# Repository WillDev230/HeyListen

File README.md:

<div align="center">

</div>
<h1></h1>
<div align="center">
HeyListen es un proyecto el cual busca disminuir la brecha de desigualdad, especificamente en el sector de las personas con nula o baja visibilidad en un contexto laboral, para brindarles la misma capacidad de ser eficientes que tienen las demas personas.
Lo lograremos brindandoles comodidades para encontrar objetos o lugares  especificos en las oficinas mediante un sonido 
</div>

<h1>Integrantes</h1>

|Integrantes   | Foto           | 
|    :---:     |     :---:      |    
| <h3>WILLIAM DAVID PINZON TORRES</h3> ||
| <h3>JOSE DANIEL BERNAL MORENO</h3>     |     |
| <h3>JUAN ESTEBAN MOZO MIGUEZ</h3>    |    |

<h1>Objetivos</h1>

* Aprender, reforzar y poner en practica conocimientos propios de la electronica
* Adquirir habilidades de liderazgo y resolucion de problemas en trabajos grupales
* adquirir habilidades de comunicacion inalambrica

<h1>Avance</h1>

* ### Caja Negra
   
* ### Caja Negra Con Tecnologia
   
  <p>Para entender mejor, se puede ver los bocetos de abajo, en especial el ultimo. </p> 
* ### Bocetos

* ### Boceto conexiones 

 * ### Boceto mecanismo 

<h1>Funcionamiento</h1>
consta de una serie de pulsadores con inscripciones en braile para su identificacion, que al ser accionados emitiran una señal, que al ser captada por otro receptor emitira un sonido durante un lapso de tiempo de 6 segundos, para que el usuario pueda ubicar su el elemento desedado
  
<h1>Aplicaciones</h1>
Las aplicaciones especificas pueden ser distintas y muy variadas pero para que en verdad sea de gran utilidad se presentan tres aplicaciones. 

### 1. Lazarillo 
Ponerle un rastreador a un baston sera de gran utilidad, pues este es un objeto relevante para las personajes de baja vision, y tambien un objeto que se puede caer o perder facilmente. No obstante para esto tendriamos que hacer que el dispositivo que tiene el boton sea movil, es decir que sea comodo y que no sea tan grande lo que puede ser un reto. 

Ejemplo: 

### 2. Controle del televisor 
De la misma manera que el anterior, estos elementos son muy faciles de perder o de refundir puesto que se utilizan bastante, entonces ponerles un rastreador a estos seria de buena utlidad

### 3. Llaves
Aunque podria ser incomodo, las llaves son uno de los elementos que mas se refunden, entonces ponerle un rastreador a las llaves puede ser muy util para una persona de baja vision. Asimismo estos elementos son demasiados importantes en la vida de las personas entonces poner un rastreador seria positivo.

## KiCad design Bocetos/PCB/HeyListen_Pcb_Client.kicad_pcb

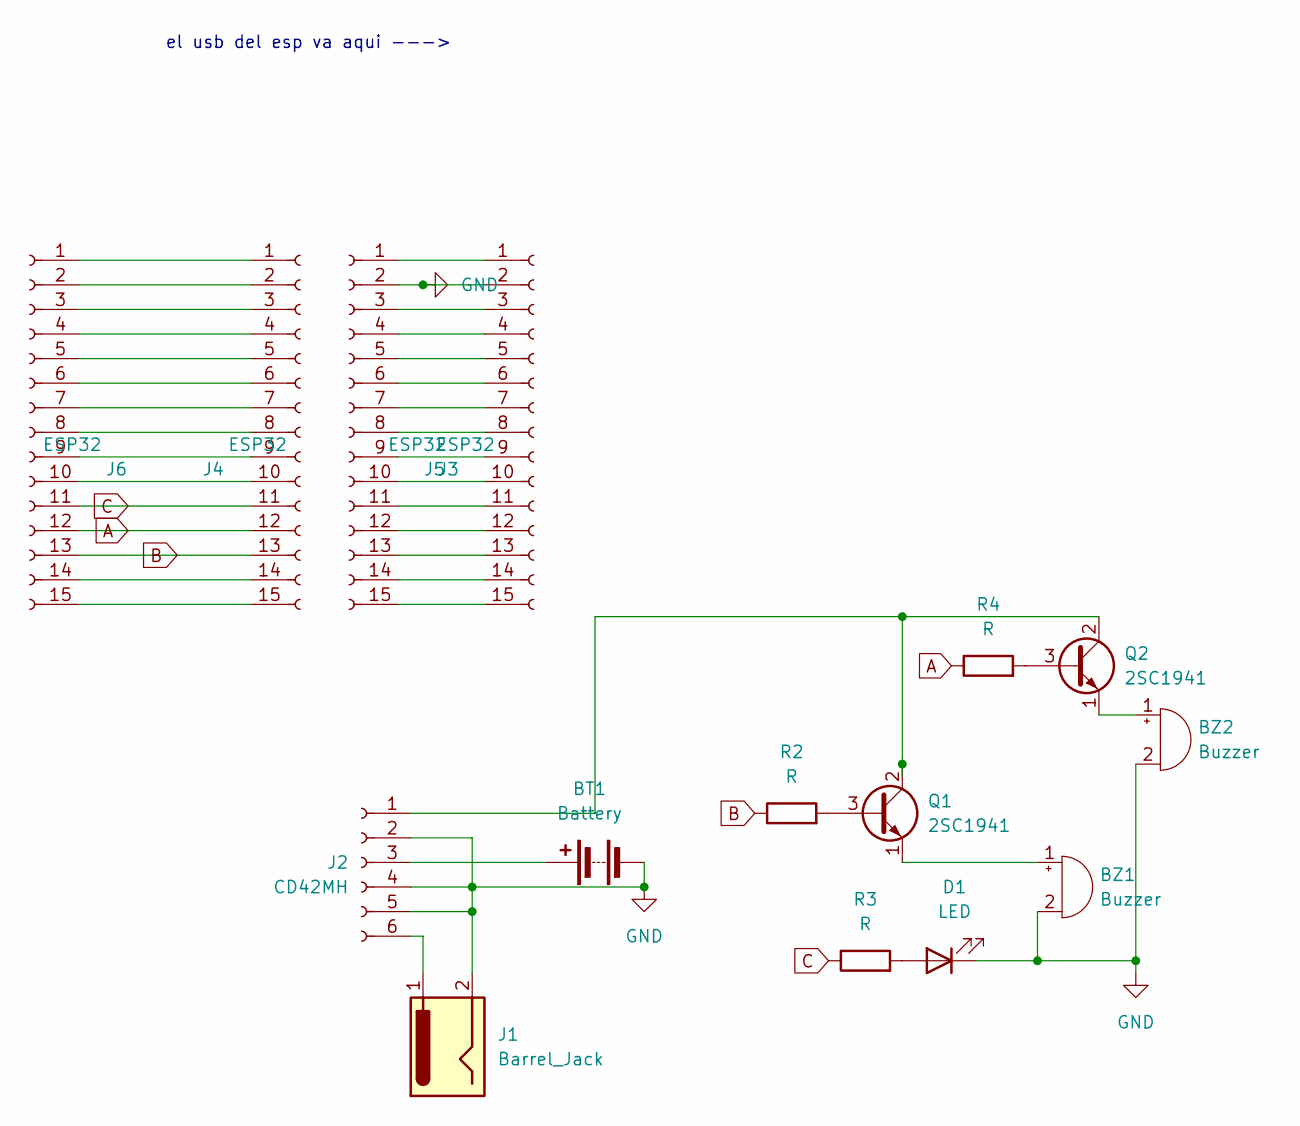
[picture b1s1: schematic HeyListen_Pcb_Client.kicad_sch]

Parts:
BT1: Battery; BatteryHolder_MPD_BH-18650-PC2
BZ1, BZ2: Buzzer; MagneticBuzzer_ProSignal_ABT-410-RC
D1: LED; LED_D3.0mm
J1: Barrel_Jack; BarrelJack_Horizontal
J2: CD42MH; PinSocket_1x06_P2.00mm_Vertical
J3, J4, J5, J6: ESP32; PinSocket_1x15_P2.00mm_Vertical
Q1, Q2: 2SC1941; TO-92_Inline
R2, R3, R4: R; R_Axial_DIN0411_L9.9mm_D3.6mm_P15.24mm_Horizontal

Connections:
A: J4.12, J6.12, R4.1
B: J4.13, J6.13, R2.1
C: J4.11, J6.11, R3.1
GND: BT1.2 (-), BZ1.2 (+), BZ2.2 (+), D1.1 (K), J1.2, J2.2, J2.4, J2.5, J3.2, J5.2
unnamed: BT1.1 (+), J2.3
unnamed: BZ1.1 (-), Q1.1 (E)
unnamed: BZ2.1 (-), Q2.1 (E)
unnamed: D1.2 (A), R3.2
unnamed: J2.1, Q1.2 (C), Q2.2 (C)
unnamed: J1.1, J2.6
unnamed: J3.1, J5.1
unnamed: J3.3, J5.3
unnamed: J3.4, J5.4
unnamed: J3.5, J5.5
unnamed: J3.6, J5.6
unnamed: J3.7, J5.7
unnamed: J3.8, J5.8
unnamed: J3.9, J5.9
unnamed: J3.10, J5.10
unnamed: J3.11, J5.11
unnamed: J3.12, J5.12
unnamed: J3.13, J5.13
unnamed: J3.14, J5.14
unnamed: J3.15, J5.15
unnamed: J4.1, J6.1
unnamed: J4.2, J6.2
unnamed: J4.3, J6.3
unnamed: J4.4, J6.4
unnamed: J4.5, J6.5
unnamed: J4.6, J6.6
unnamed: J4.7, J6.7
unnamed: J4.8, J6.8
unnamed: J4.9, J6.9
unnamed: J4.10, J6.10
unnamed: J4.14, J6.14
unnamed: J4.15, J6.15
unnamed: Q1.3 (B), R2.2
unnamed: Q2.3 (B), R4.2

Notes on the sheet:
el usb del esp va aqui --->

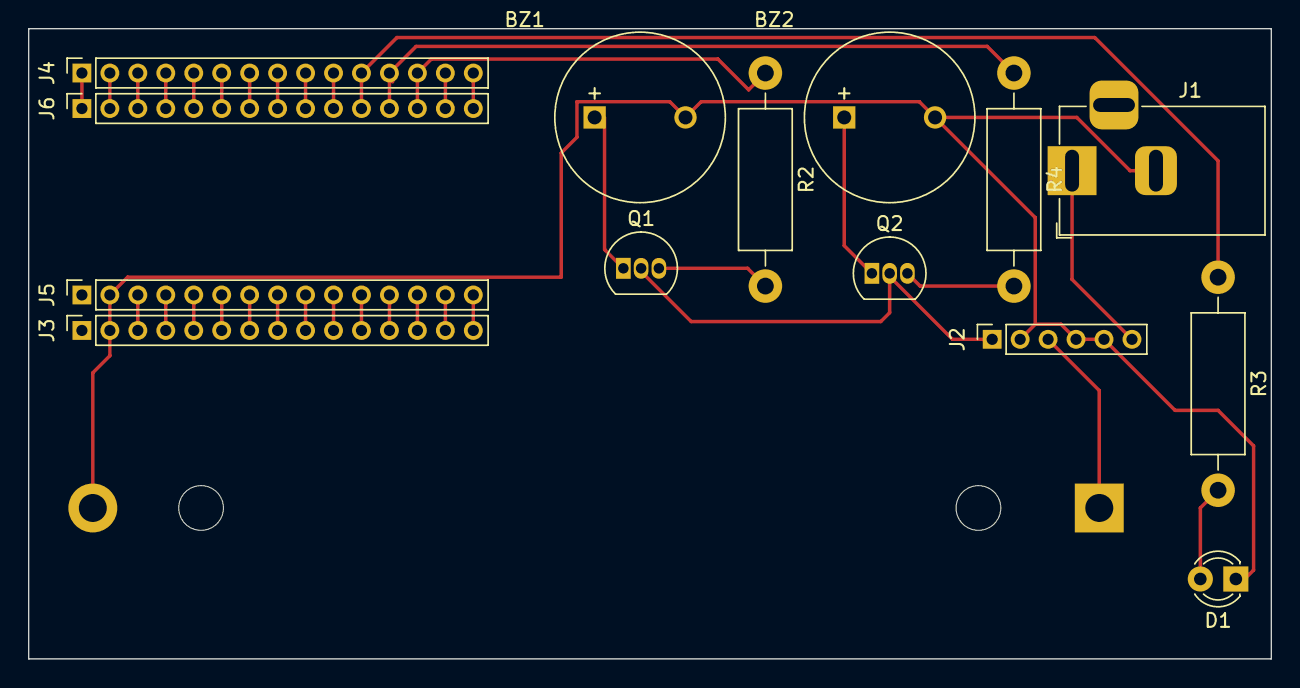
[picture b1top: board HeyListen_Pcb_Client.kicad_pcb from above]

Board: 2 copper layers, 88.9 x 45.1 mm, 15 parts (1 on the bottom side), 38 nets.

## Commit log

2023-11-05 Create a
2023-11-27 Create 1- HOME
2023-11-27 Create si
2023-11-27 Create no
2023-11-27 Create talvez
2023-11-27 Create ok si
2023-11-27 Create ok no
2023-11-27 Create Codigo final Emisor
2023-11-27 Create Codigo final receptor
